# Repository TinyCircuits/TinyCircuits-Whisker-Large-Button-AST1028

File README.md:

# TinyCircuits Wireling Large Button
# AST1028 Rev1

The design files are located under design_files/ for the TinyCircuits AST1028 Rev 1 PCB. This is a Wireling board which features a large button to add an easy input to a project. 

Format is in Cadsoft Eagle format - Eagle version 6.2 was used for the original design.

For more infomation on this, check out the product page at TinyCircuits.com

# License:

Design by TinyCircuits.
All design files are released under the Creative Commons Attribution Share-Alike 3.0 License, see the following link for details: http://creativecommons.org/licenses/by-sa/3.0

All text above must be included in any redistribution or derived design

This project uses designs and concepts developed as part of the Arduino project and the LilyPad project.  The TinyCircuits design files themselves (schematics, PCB and libraries) are not directly derived from these works' design files and have been created new, however the concepts and basic architecture behind the TinyDuino and TinyLily products are derived and we thank the hard work of the organizations below for their contributions to open-source hardware:
  
Original Arduino Uno Design by Team Arduino

LilyPad Arduino Design by Leah Buechley and Sparkfun Electronics

Please support the open-source hardware community

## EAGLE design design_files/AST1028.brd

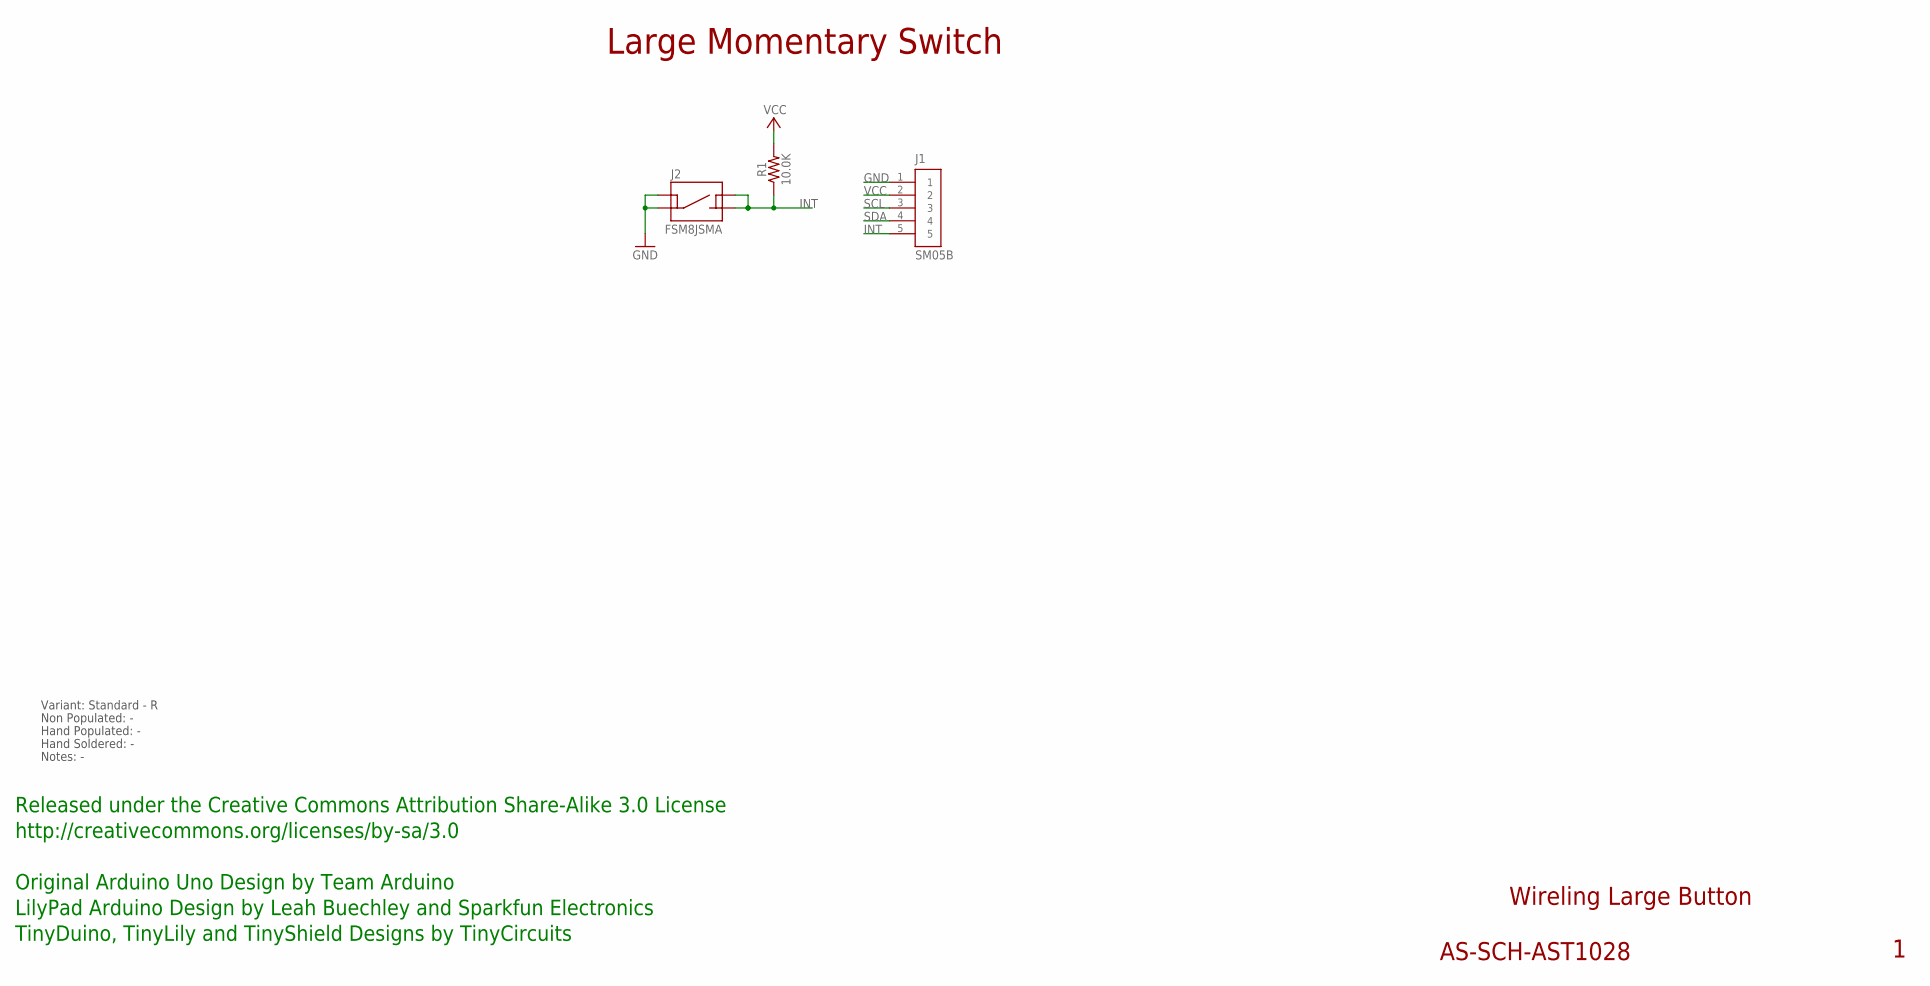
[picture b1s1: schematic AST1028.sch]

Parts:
J1: SM05B; JST_SH_5X1_EDGE
J2: FSM8JSMA; SWITCH-FSM/JSM
R1: 10.0K; 0402

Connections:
GND: J1.1, J2.P$1 (3), J2.P$4 (1)
INT: J1.5, J2.P$2 (4), J2.P$3 (2), R1.1
SCL: J1.3
SDA: J1.4
VCC: J1.2, R1.2

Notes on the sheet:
Wireling Large Button
AS-SCH-AST1028
Large Momentary Switch
Released under the Creative Commons Attribution Share-Alike 3.0 License
http://creativecommons.org/licenses/by-sa/3.0
Original Arduino Uno Design by Team Arduino
TinyDuino, TinyLily and TinyShield Designs by TinyCircuits
LilyPad Arduino Design by Leah Buechley and Sparkfun Electronics
Non Populated: -
Hand Populated: -
Hand Soldered: -
Notes: -
Variant: Standard - R

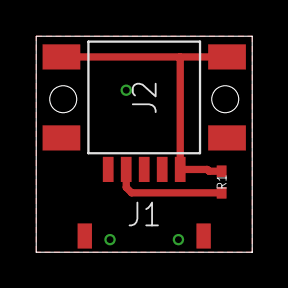
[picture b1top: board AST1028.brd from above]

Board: 2 copper layers, 12.0 x 12.0 mm, 4 parts (0 on the bottom side), 3 nets.

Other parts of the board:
U$1: DOCFIELD-TINYCIRCUITS-PCB

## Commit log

2019-07-30 added example sketch
2019-07-30 updated to use Port 0
2019-07-30 cleaned up code
2019-09-18 datasheet
2019-10-29 name update
2019-12-02 images
2019-12-04 code
2019-12-17 updated documentation
2020-01-07 added new button/switch example
2020-01-10 image update
2020-02-04 mass image update
2020-08-14 Add CAD data
